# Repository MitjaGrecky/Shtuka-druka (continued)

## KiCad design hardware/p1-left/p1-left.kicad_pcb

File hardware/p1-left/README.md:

# P1 - Left deck (time column)

19 buttons with 2 RGB each (P101), an I2C multiplexer (P99), the deck bus to P2 (P100) and the module buses to M3 and W1.
Spec: `hardware/for-routing/SPEC_boards.md`, section P1. Status: rev 0.2 by the Rev 0.2 section below (R170, 16.11.2026; commit `decdae9`) - schematic and placed board, not routed (`UNROUTED`). Generator `REV` and the silk text still say 0.1 (not bumped in `decdae9`): the schematic owner should set `REV = "0.2"` and regenerate.
Package: `hardware/for-routing/P1/`. P99, P100, P101 are proposals: change them through the constants in `gen/design.py`.

| | |
|---|---|
| Board | 92 x 258 mm, 2 layers; panel x 10-102, y 4-262 |
| Top side | 19 x TS-1187A (C318884): Rec, Play, Stop, Restart, Metronome, Tap, Capture, Resample, Undo, Redo, Delete, Duplicate, Double, New, Quantize, Length, Automate, Repeat, Accent at their layout_v7 places; 38 x XL-1615RGBC-RF 6.5 mm left and right |
| Bottom side | 2 x LP5864 (U1 cell A 0x40: buttons 1-12, U2 cell B 0x41: 13-19) among their buttons; 3 x 74HC165 near their rows; TCA9546APWR (U6) near J1 |
| Buses | J1 2 x 8 to P2 at the right edge (P100: pins 1-14 as the module bus, 15 AUX unused, 16 GND); J2 2 x 7 to M3 and J3 2 x 7 to W1 at the rear edge |
| I2C | TCA9546A 0x70 (A2 A1 A0 via 0R to GND): ch 0 own LP5864s, ch 1 J2 (M3), ch 2 J3 (W1), ch 3 free; 4.7k pull-ups on ch 0-2, upstream pull-ups on P2 |
| Shift chain | P2 reads U3 (D7 Rec ... ), U4, U5 (bits 20-24 read 1), then M3 (J2), then W1 (J3), which continues to M5; W1's SR_IN pulled up here (R1); J1 pin 14 unused |
| ~INT | J2 and J3 ~INT go straight to J1 |
| Holes | 14 x M2: corners, short-side middles, long sides at rows without buttons (y 60, 97.5, 150, 197.5), at most 60 mm apart |

Checks (13.11.2026, PC): EasyEDA Pro import (project P1_v1): PCB 83/83 and schematic 83/83 nets, 110/110 parts, against a
reference netlist written from `design.py`. ERC, DRC, parity: CI (kicad-cli crashes this PC). No `schematic.pdf`/`outline.dxf` yet.
The TCA9546A symbol is converted from KiCad 10's library to the KiCad 7 format by `hardware/common/gen/sym7.py`.

Open: LCSC number of TCA9546APWR (to choose, P99); J2/J3 places at the rear edge follow M3's and W1's connectors (both near panel x 56) - set apart (x 40 and 72) so the two ribbons do not collide.

Generators: `gen/design.py`, `gen/make_sch.py`, `gen/check_netlist.py`, `gen/make_pcb.py` (shared blocks: `hardware/common/gen/kit.py` - `deck_inputs`, `i2c_mux`, `deck_bus`).

License: CERN-OHL-S-2.0 (hardware), AGPL-3.0-or-later (scripts).

Rev 0.2 (16.11.2026): R170 (16.11.2026): шинные разъёмы снизу лежачие (угловые): HX PZ1.27-2x7P WZ / 2x8P WZ (C22438113 / C22438114), J1 открыт к P2 (у P1 вправо, у P3 и P4 влево), J2–J4 к заднему краю; на P4 штекер колеса — JST S2B-PH-K-S (C173752, 179 611 шт.). Вертикальная вилка с IDC (≈ 7,5 мм) при 8 мм до дна не оставляла места на изгиб кабеля.

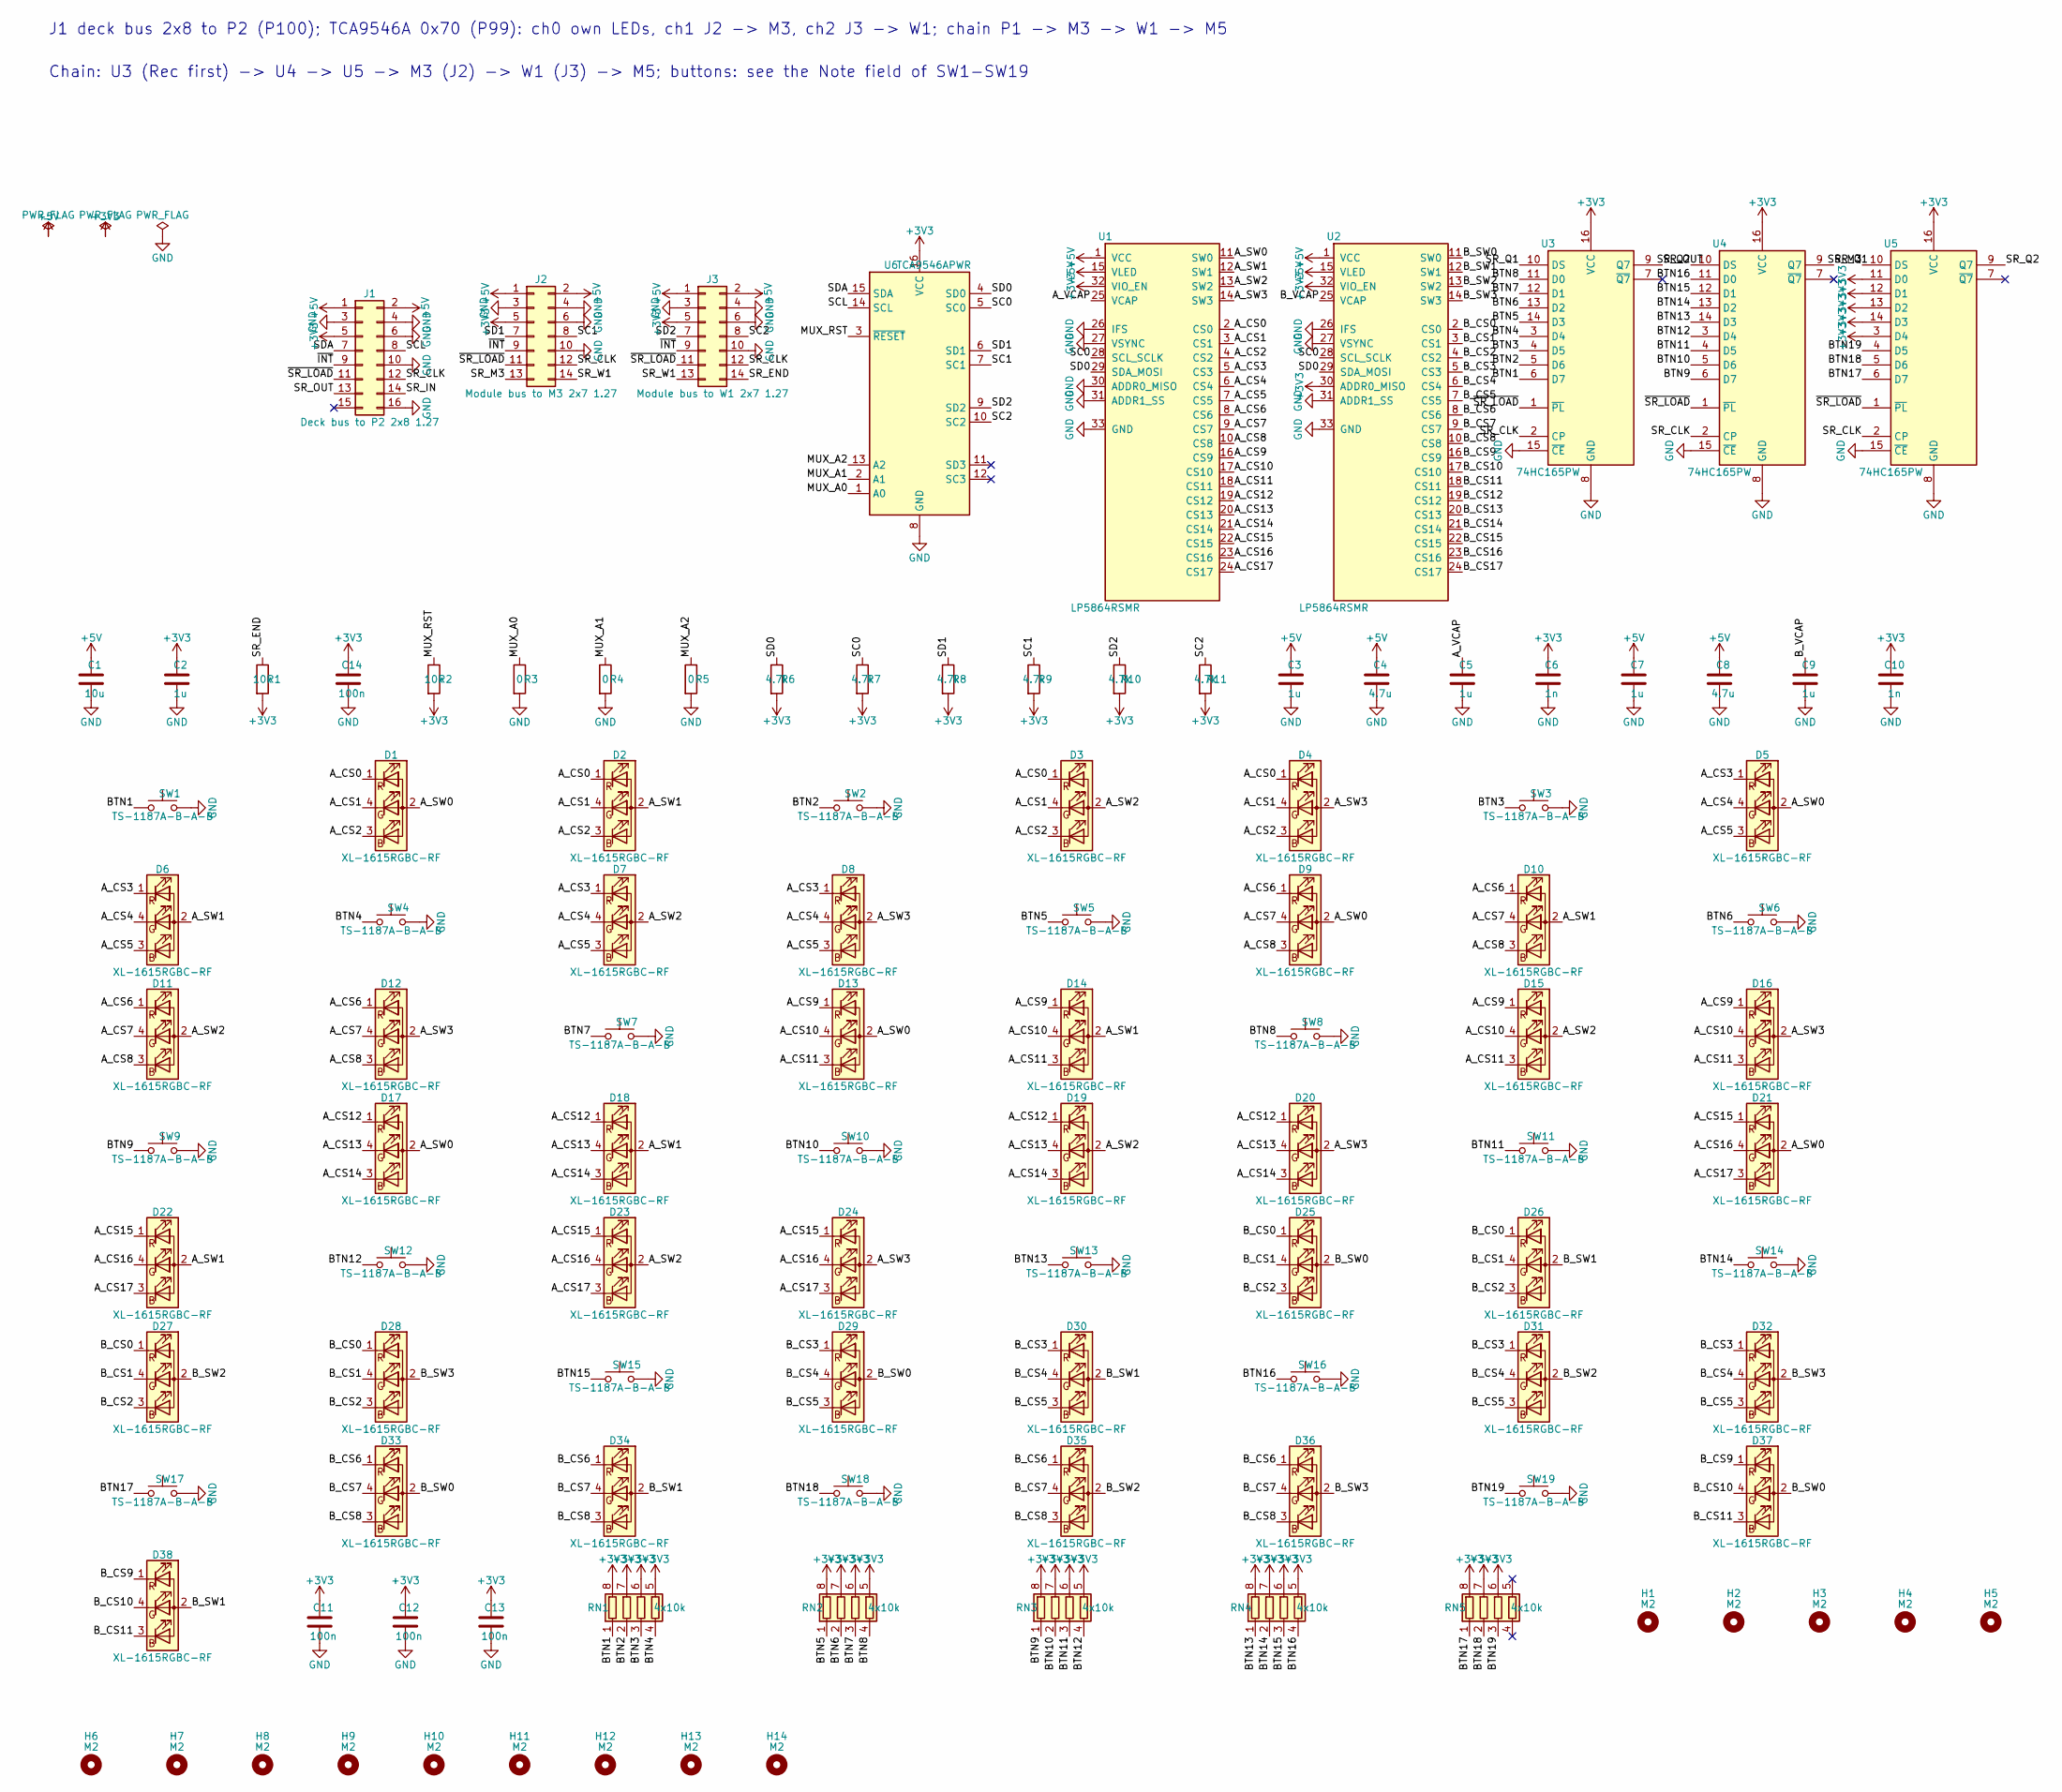
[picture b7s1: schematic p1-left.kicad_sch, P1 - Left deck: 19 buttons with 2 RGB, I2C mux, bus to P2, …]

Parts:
C1: 10u; C_0805_2012Metric; LCSC C15850
C2, C3, C5, C7, C9: 1u; C_0402_1005Metric; LCSC C52923
C4, C8: 4.7u; C_0805_2012Metric; LCSC C1779
C6, C10: 1n; C_0402_1005Metric; LCSC C1523
C11, C12, C13, C14: 100n; C_0402_1005Metric; LCSC C1525
D1, D2, D3, D4, D5, D6, D7, D8, D9, D10, D11, D12, D13, D14, D15, D16, D17, D18, D19, D20, D21, D22, D23, D24, D25, D26, D27, D28, D29, D30, D31, D32, D33, D34, D35, D36, D37, D38: XL-1615RGBC-RF; LED_RGB_XL-1615RGBC_1.6x1.5mm; LCSC C965840
H1, H2, H3, H4, H5, H6, H7, H8, H9, H10, H11, H12, H13, H14: M2; MountingHole_2.2mm_M2
J1: Deck bus to P2 2x8 1.27; PinHeader_2x08_P1.27mm_Horizontal; LCSC C22438114
J2: Module bus to M3 2x7 1.27; PinHeader_2x07_P1.27mm_Horizontal; LCSC C22438113
J3: Module bus to W1 2x7 1.27; PinHeader_2x07_P1.27mm_Horizontal; LCSC C22438113
R1, R2: 10k; R_0402_1005Metric; LCSC C25744
R3, R4, R5: 0; R_0402_1005Metric; LCSC C17168
R6, R7, R8, R9, R10, R11: 4.7k; R_0402_1005Metric; LCSC C25900
RN1, RN2, RN3, RN4, RN5: 4x10k; R_Array_Convex_4x0402; LCSC C25725
SW1, SW2, SW3, SW4, SW5, SW6, SW7, SW8, SW9, SW10, SW11, SW12, SW13, SW14, SW15, SW16, SW17, SW18, SW19: TS-1187A-B-A-B; SW_Push_1P1T_XKB_TS-1187A; LCSC C318884
U1, U2: LP5864RSMR; VQFN-32-1EP_4x4mm_P0.4mm_EP2.8x2.8mm; LCSC C5220564
U3, U4, U5: 74HC165PW; TSSOP-16_4.4x5mm_P0.65mm; LCSC C80696
U6: TCA9546APWR; TSSOP-16_4.4x5mm_P0.65mm; LCSC C201653

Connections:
+3V3: C2.1, C6.1, C10.1, C11.1, C12.1, C13.1, C14.1, J1.5, J2.5, J3.5, R1.2, R2.2, R6.2, R7.2, R8.2, R9.2, R10.2, R11.2, RN1.5 (R4.2), RN1.6 (R3.2), RN1.7 (R2.2), RN1.8 (R1.2), RN2.5 (R4.2), RN2.6 (R3.2), RN2.7 (R2.2), RN2.8 (R1.2), RN3.5 (R4.2), RN3.6 (R3.2), RN3.7 (R2.2), RN3.8 (R1.2), RN4.5 (R4.2), RN4.6 (R3.2), RN4.7 (R2.2), RN4.8 (R1.2), RN5.6 (R3.2), RN5.7 (R2.2), RN5.8 (R1.2), U1.32 (VIO_EN), U2.30 (ADDR0_MISO), U2.32 (VIO_EN), U3.16 (VCC), U4.16 (VCC), U5.3 (D4), U5.11 (D0), U5.12 (D1), U5.13 (D2), U5.14 (D3), U5.16 (VCC), U6.16 (VCC)
+5V: C1.1, C3.1, C4.1, C7.1, C8.1, J1.1, J1.2, J2.1, J2.2, J3.1, J3.2, U1.1 (VCC), U1.15 (VLED), U2.1 (VCC), U2.15 (VLED)
/A_CS0: D1.1 (RK), D2.1 (RK), D3.1 (RK), D4.1 (RK), U1.2 (CS0)
/A_CS1: D1.4 (GK), D2.4 (GK), D3.4 (GK), D4.4 (GK), U1.3 (CS1)
/A_CS2: D1.3 (BK), D2.3 (BK), D3.3 (BK), D4.3 (BK), U1.4 (CS2)
/A_CS3: D5.1 (RK), D6.1 (RK), D7.1 (RK), D8.1 (RK), U1.5 (CS3)
/A_CS4: D5.4 (GK), D6.4 (GK), D7.4 (GK), D8.4 (GK), U1.6 (CS4)
/A_CS5: D5.3 (BK), D6.3 (BK), D7.3 (BK), D8.3 (BK), U1.7 (CS5)
/A_CS6: D9.1 (RK), D10.1 (RK), D11.1 (RK), D12.1 (RK), U1.8 (CS6)
/A_CS7: D9.4 (GK), D10.4 (GK), D11.4 (GK), D12.4 (GK), U1.9 (CS7)
/A_CS8: D9.3 (BK), D10.3 (BK), D11.3 (BK), D12.3 (BK), U1.10 (CS8)
/A_CS9: D13.1 (RK), D14.1 (RK), D15.1 (RK), D16.1 (RK), U1.16 (CS9)
/A_CS10: D13.4 (GK), D14.4 (GK), D15.4 (GK), D16.4 (GK), U1.17 (CS10)
/A_CS11: D13.3 (BK), D14.3 (BK), D15.3 (BK), D16.3 (BK), U1.18 (CS11)
/A_CS12: D17.1 (RK), D18.1 (RK), D19.1 (RK), D20.1 (RK), U1.19 (CS12)
/A_CS13: D17.4 (GK), D18.4 (GK), D19.4 (GK), D20.4 (GK), U1.20 (CS13)
/A_CS14: D17.3 (BK), D18.3 (BK), D19.3 (BK), D20.3 (BK), U1.21 (CS14)
/A_CS15: D21.1 (RK), D22.1 (RK), D23.1 (RK), D24.1 (RK), U1.22 (CS15)
/A_CS16: D21.4 (GK), D22.4 (GK), D23.4 (GK), D24.4 (GK), U1.23 (CS16)
/A_CS17: D21.3 (BK), D22.3 (BK), D23.3 (BK), D24.3 (BK), U1.24 (CS17)
/A_SW0: D1.2 (A), D5.2 (A), D9.2 (A), D13.2 (A), D17.2 (A), D21.2 (A), U1.11 (SW0)
/A_SW1: D2.2 (A), D6.2 (A), D10.2 (A), D14.2 (A), D18.2 (A), D22.2 (A), U1.12 (SW1)
/A_SW2: D3.2 (A), D7.2 (A), D11.2 (A), D15.2 (A), D19.2 (A), D23.2 (A), U1.13 (SW2)
/A_SW3: D4.2 (A), D8.2 (A), D12.2 (A), D16.2 (A), D20.2 (A), D24.2 (A), U1.14 (SW3)
/A_VCAP: C5.1, U1.25 (VCAP)
/BTN1: RN1.1 (R1.1), SW1.1, U3.6 (D7)
/BTN2: RN1.2 (R2.1), SW2.1, U3.5 (D6)
/BTN3: RN1.3 (R3.1), SW3.1, U3.4 (D5)
/BTN4: RN1.4 (R4.1), SW4.1, U3.3 (D4)
/BTN5: RN2.1 (R1.1), SW5.1, U3.14 (D3)
/BTN6: RN2.2 (R2.1), SW6.1, U3.13 (D2)
/BTN7: RN2.3 (R3.1), SW7.1, U3.12 (D1)
/BTN8: RN2.4 (R4.1), SW8.1, U3.11 (D0)
/BTN9: RN3.1 (R1.1), SW9.1, U4.6 (D7)
/BTN10: RN3.2 (R2.1), SW10.1, U4.5 (D6)
/BTN11: RN3.3 (R3.1), SW11.1, U4.4 (D5)
/BTN12: RN3.4 (R4.1), SW12.1, U4.3 (D4)
/BTN13: RN4.1 (R1.1), SW13.1, U4.14 (D3)
/BTN14: RN4.2 (R2.1), SW14.1, U4.13 (D2)
/BTN15: RN4.3 (R3.1), SW15.1, U4.12 (D1)
/BTN16: RN4.4 (R4.1), SW16.1, U4.11 (D0)
/BTN17: RN5.1 (R1.1), SW17.1, U5.6 (D7)
/BTN18: RN5.2 (R2.1), SW18.1, U5.5 (D6)
/BTN19: RN5.3 (R3.1), SW19.1, U5.4 (D5)
/B_CS0: D25.1 (RK), D26.1 (RK), D27.1 (RK), D28.1 (RK), U2.2 (CS0)
/B_CS1: D25.4 (GK), D26.4 (GK), D27.4 (GK), D28.4 (GK), U2.3 (CS1)
/B_CS2: D25.3 (BK), D26.3 (BK), D27.3 (BK), D28.3 (BK), U2.4 (CS2)
/B_CS3: D29.1 (RK), D30.1 (RK), D31.1 (RK), D32.1 (RK), U2.5 (CS3)
/B_CS4: D29.4 (GK), D30.4 (GK), D31.4 (GK), D32.4 (GK), U2.6 (CS4)
/B_CS5: D29.3 (BK), D30.3 (BK), D31.3 (BK), D32.3 (BK), U2.7 (CS5)
/B_CS6: D33.1 (RK), D34.1 (RK), D35.1 (RK), D36.1 (RK), U2.8 (CS6)
/B_CS7: D33.4 (GK), D34.4 (GK), D35.4 (GK), D36.4 (GK), U2.9 (CS7)
/B_CS8: D33.3 (BK), D34.3 (BK), D35.3 (BK), D36.3 (BK), U2.10 (CS8)
/B_CS9: D37.1 (RK), D38.1 (RK), U2.16 (CS9)
/B_CS10: D37.4 (GK), D38.4 (GK), U2.17 (CS10)
/B_CS11: D37.3 (BK), D38.3 (BK), U2.18 (CS11)
/B_CS12: U2.19 (CS12)
/B_CS13: U2.20 (CS13)
/B_CS14: U2.21 (CS14)
/B_CS15: U2.22 (CS15)
/B_CS16: U2.23 (CS16)
/B_CS17: U2.24 (CS17)
/B_SW0: D25.2 (A), D29.2 (A), D33.2 (A), D37.2 (A), U2.11 (SW0)
/B_SW1: D26.2 (A), D30.2 (A), D34.2 (A), D38.2 (A), U2.12 (SW1)
/B_SW2: D27.2 (A), D31.2 (A), D35.2 (A), U2.13 (SW2)
/B_SW3: D28.2 (A), D32.2 (A), D36.2 (A), U2.14 (SW3)
/B_VCAP: C9.1, U2.25 (VCAP)
/MUX_A0: R3.1, U6.1 (A0)
/MUX_A1: R4.1, U6.2 (A1)
/MUX_A2: R5.1, U6.13 (A2)
/MUX_RST: R2.1, U6.3 (~RESET)
/SC0: R7.1, U1.28 (SCL_SCLK), U2.28 (SCL_SCLK), U6.5 (SC0)
/SC1: J2.8, R9.1, U6.7 (SC1)
/SC2: J3.8, R11.1, U6.10 (SC2)
/SCL: J1.8, U6.14 (SCL)
/SD0: R6.1, U1.29 (SDA_MOSI), U2.29 (SDA_MOSI), U6.4 (SD0)
/SD1: J2.7, R8.1, U6.6 (SD1)
/SD2: J3.7, R10.1, U6.9 (SD2)
/SDA: J1.7, U6.15 (SDA)
/SR_CLK: J1.12, J2.12, J3.12, U3.2 (CP), U4.2 (CP), U5.2 (CP)
/SR_END: J3.14, R1.1
/SR_IN: J1.14
/SR_M3: J2.13, U5.10 (DS)
/SR_OUT: J1.13, U3.9 (Q7)
/SR_Q1: U3.10 (DS), U4.9 (Q7)
/SR_Q2: U4.10 (DS), U5.9 (Q7)
/SR_W1: J2.14, J3.13
/~INT: J1.9, J2.9, J3.9
/~SR_LOAD: J1.11, J2.11, J3.11, U3.1 (~PL), U4.1 (~PL), U5.1 (~PL)
GND: C1.2, C2.2, C3.2, C4.2, C5.2, C6.2, C7.2, C8.2, C9.2, C10.2, C11.2, C12.2, C13.2, C14.2, J1.3, J1.4, J1.6, J1.10, J1.16, J2.3, J2.4, J2.6, J2.10, J3.3, J3.4, J3.6, J3.10, R3.2, R4.2, R5.2, SW1.2, SW2.2, SW3.2, SW4.2, SW5.2, SW6.2, SW7.2, SW8.2, SW9.2, SW10.2, SW11.2, SW12.2, SW13.2, SW14.2, SW15.2, SW16.2, SW17.2, SW18.2, SW19.2, U1.26 (IFS), U1.27 (VSYNC), U1.30 (ADDR0_MISO), U1.31 (ADDR1_SS), U1.33 (GND), U2.26 (IFS), U2.27 (VSYNC), U2.31 (ADDR1_SS), U2.33 (GND), U3.8 (GND), U3.15 (~CE), U4.8 (GND), U4.15 (~CE), U5.8 (GND), U5.15 (~CE), U6.8 (GND)

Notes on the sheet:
J1 deck bus 2x8 to P2 (P100); TCA9546A 0x70 (P99): ch0 own LEDs, ch1 J2 -> M3, ch2 J3 -> W1; chain P1 -> M3 -> W1 -> M5
Chain: U3 (Rec first) -> U4 -> U5 -> M3 (J2) -> W1 (J3) -> M5; buttons: see the Note field of SW1-SW19

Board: 2 copper layers, 110 parts (39 on the bottom side), 83 nets, no tracks yet.

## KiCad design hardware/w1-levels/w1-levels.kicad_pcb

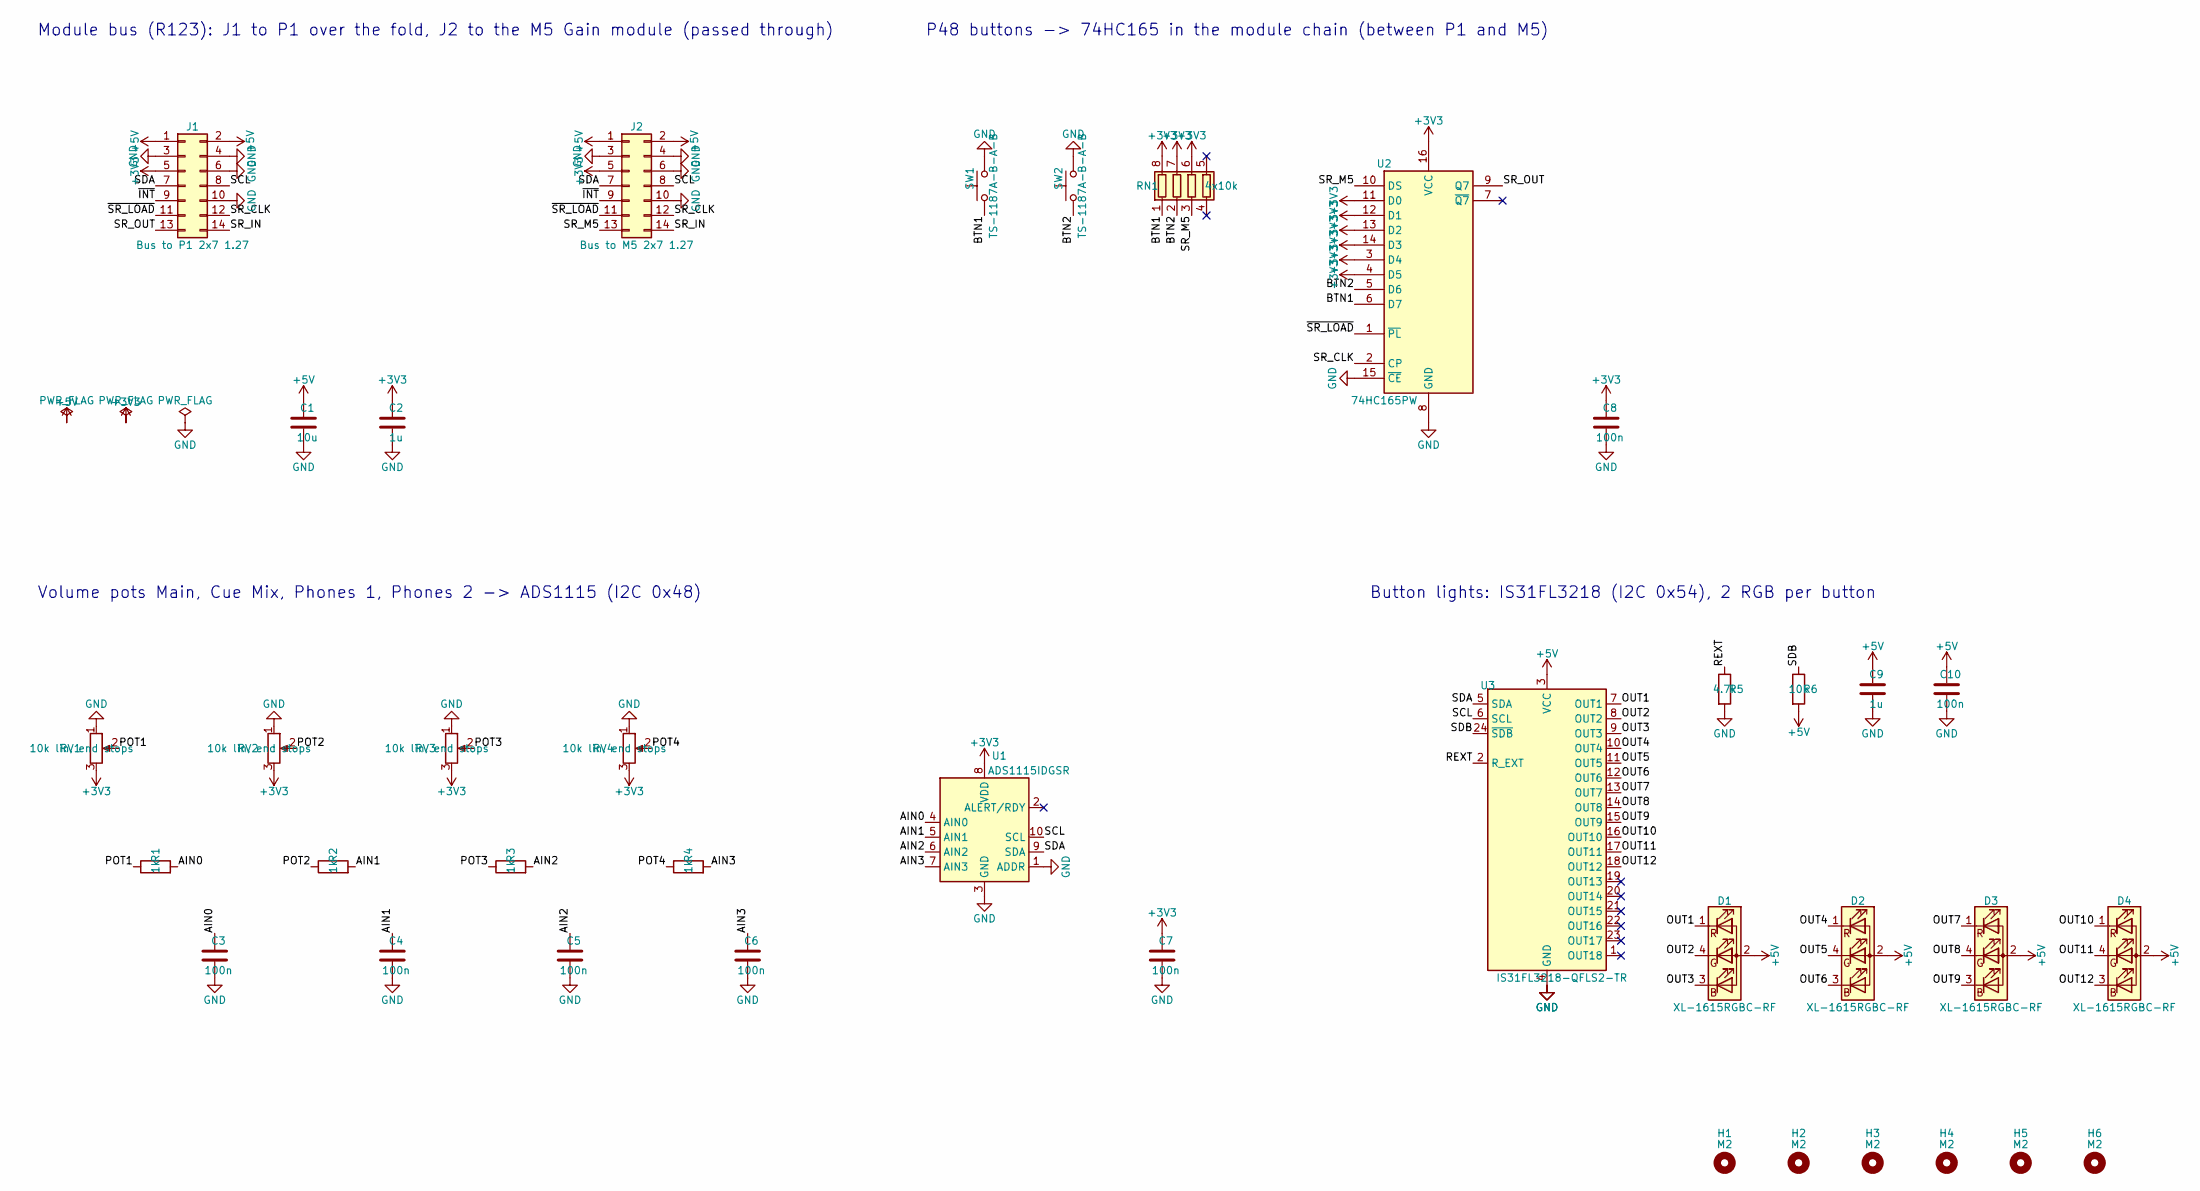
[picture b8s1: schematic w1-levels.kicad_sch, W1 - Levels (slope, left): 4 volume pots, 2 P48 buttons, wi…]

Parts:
C1: 10u; C_0805_2012Metric; LCSC C15850
C2, C9: 1u; C_0402_1005Metric; LCSC C52923
C3, C4, C5, C6, C7, C8, C10: 100n; C_0402_1005Metric; LCSC C1525
D1, D2, D3, D4: XL-1615RGBC-RF; LED_RGB_XL-1615RGBC_1.6x1.5mm; LCSC C965840
H1, H2, H3, H4, H5, H6: M2; MountingHole_2.2mm_M2
J1: Bus to P1 2x7 1.27; PinHeader_2x07_P1.27mm_Vertical; LCSC C5372811
J2: Bus to M5 2x7 1.27; PinHeader_2x07_P1.27mm_Vertical; LCSC C5372811
R1, R2, R3, R4: 1k; R_0402_1005Metric; LCSC C11702
R5: 4.7k; R_0402_1005Metric; LCSC C25900
R6: 10k; R_0402_1005Metric; LCSC C25744
RN1: 4x10k; R_Array_Convex_4x0402; LCSC C25725
RV1, RV2, RV3, RV4: 10k lin, end stops; Potentiometer_Alps_RK09K_Single_Vertical; Part Alps RK09K1130A5R (shaft; was A6S, rev 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; LCSC C209779
SW1, SW2: TS-1187A-B-A-B; SW_Push_1P1T_XKB_TS-1187A; LCSC C318884
U1: ADS1115IDGSR; TSSOP-10_3x3mm_P0.5mm; LCSC C37593
U2: 74HC165PW; TSSOP-16_4.4x5mm_P0.65mm; LCSC C80696
U3: IS31FL3218-QFLS2-TR; QFN-24-1EP_4x4mm_P0.5mm_EP2.7x2.7mm; LCSC C2940546

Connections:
+3V3: C2.1, C7.1, C8.1, J1.5, J2.5, RN1.6 (R3.2), RN1.7 (R2.2), RN1.8 (R1.2), RV1.3, RV2.3, RV3.3, RV4.3, U1.8 (VDD), U2.3 (D4), U2.4 (D5), U2.11 (D0), U2.12 (D1), U2.13 (D2), U2.14 (D3), U2.16 (VCC)
+5V: C1.1, C9.1, C10.1, D1.2 (A), D2.2 (A), D3.2 (A), D4.2 (A), J1.1, J1.2, J2.1, J2.2, R6.2, U3.3 (VCC)
/AIN0: C3.1, R1.2, U1.4 (AIN0)
/AIN1: C4.1, R2.2, U1.5 (AIN1)
/AIN2: C5.1, R3.2, U1.6 (AIN2)
/AIN3: C6.1, R4.2, U1.7 (AIN3)
/BTN1: RN1.1 (R1.1), SW1.1, U2.6 (D7)
/BTN2: RN1.2 (R2.1), SW2.1, U2.5 (D6)
/OUT1: D1.1 (RK), U3.7 (OUT1)
/OUT2: D1.4 (GK), U3.8 (OUT2)
/OUT3: D1.3 (BK), U3.9 (OUT3)
/OUT4: D2.1 (RK), U3.10 (OUT4)
/OUT5: D2.4 (GK), U3.11 (OUT5)
/OUT6: D2.3 (BK), U3.12 (OUT6)
/OUT7: D3.1 (RK), U3.13 (OUT7)
/OUT8: D3.4 (GK), U3.14 (OUT8)
/OUT9: D3.3 (BK), U3.15 (OUT9)
/OUT10: D4.1 (RK), U3.16 (OUT10)
/OUT11: D4.4 (GK), U3.17 (OUT11)
/OUT12: D4.3 (BK), U3.18 (OUT12)
/POT1: R1.1, RV1.2
/POT2: R2.1, RV2.2
/POT3: R3.1, RV3.2
/POT4: R4.1, RV4.2
/REXT: R5.1, U3.2 (R_EXT)
/SCL: J1.8, J2.8, U1.10 (SCL), U3.6 (SCL)
/SDA: J1.7, J2.7, U1.9 (SDA), U3.5 (SDA)
/SDB: R6.1, U3.24 (~SDB)
/SR_CLK: J1.12, J2.12, U2.2 (CP)
/SR_IN: J1.14, J2.14
/SR_M5: J2.13, RN1.3 (R3.1), U2.10 (DS)
/SR_OUT: J1.13, U2.9 (Q7)
/~INT: J1.9, J2.9
/~SR_LOAD: J1.11, J2.11, U2.1 (~PL)
GND: C1.2, C2.2, C3.2, C4.2, C5.2, C6.2, C7.2, C8.2, C9.2, C10.2, J1.3, J1.4, J1.6, J1.10, J2.3, J2.4, J2.6, J2.10, R5.2, RV1.1, RV2.1, RV3.1, RV4.1, SW1.2, SW2.2, U1.1 (ADDR), U1.3 (GND), U2.8 (GND), U2.15 (~CE), U3.4 (GND), U3.25 (GND)

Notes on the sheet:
Module bus (R123): J1 to P1 over the fold, J2 to the M5 Gain module (passed through)
Volume pots Main, Cue Mix, Phones 1, Phones 2 -> ADS1115 (I2C 0x48)
P48 buttons -> 74HC165 in the module chain (between P1 and M5)
Button lights: IS31FL3218 (I2C 0x54), 2 RGB per button

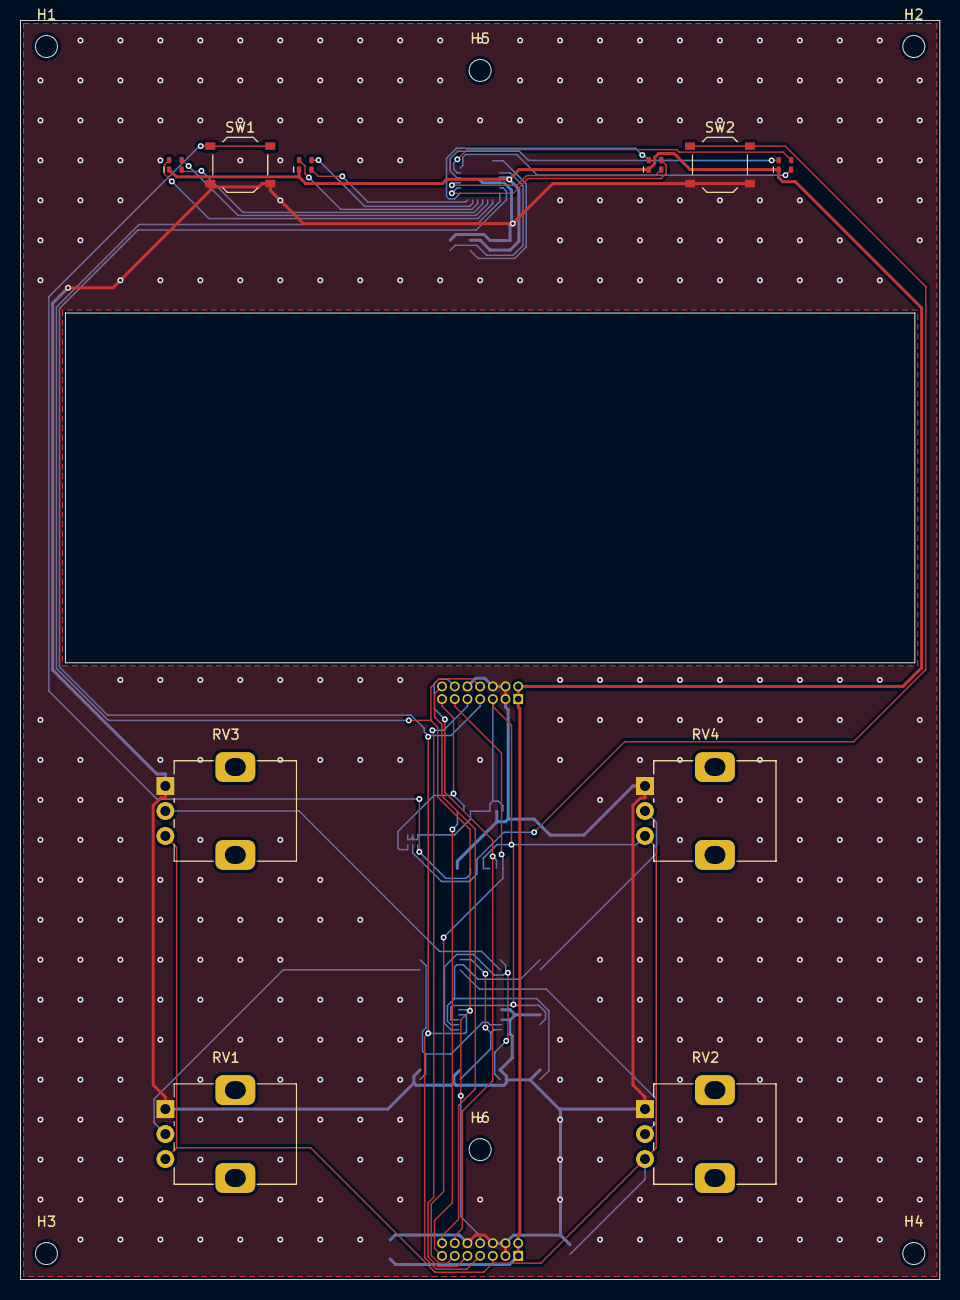
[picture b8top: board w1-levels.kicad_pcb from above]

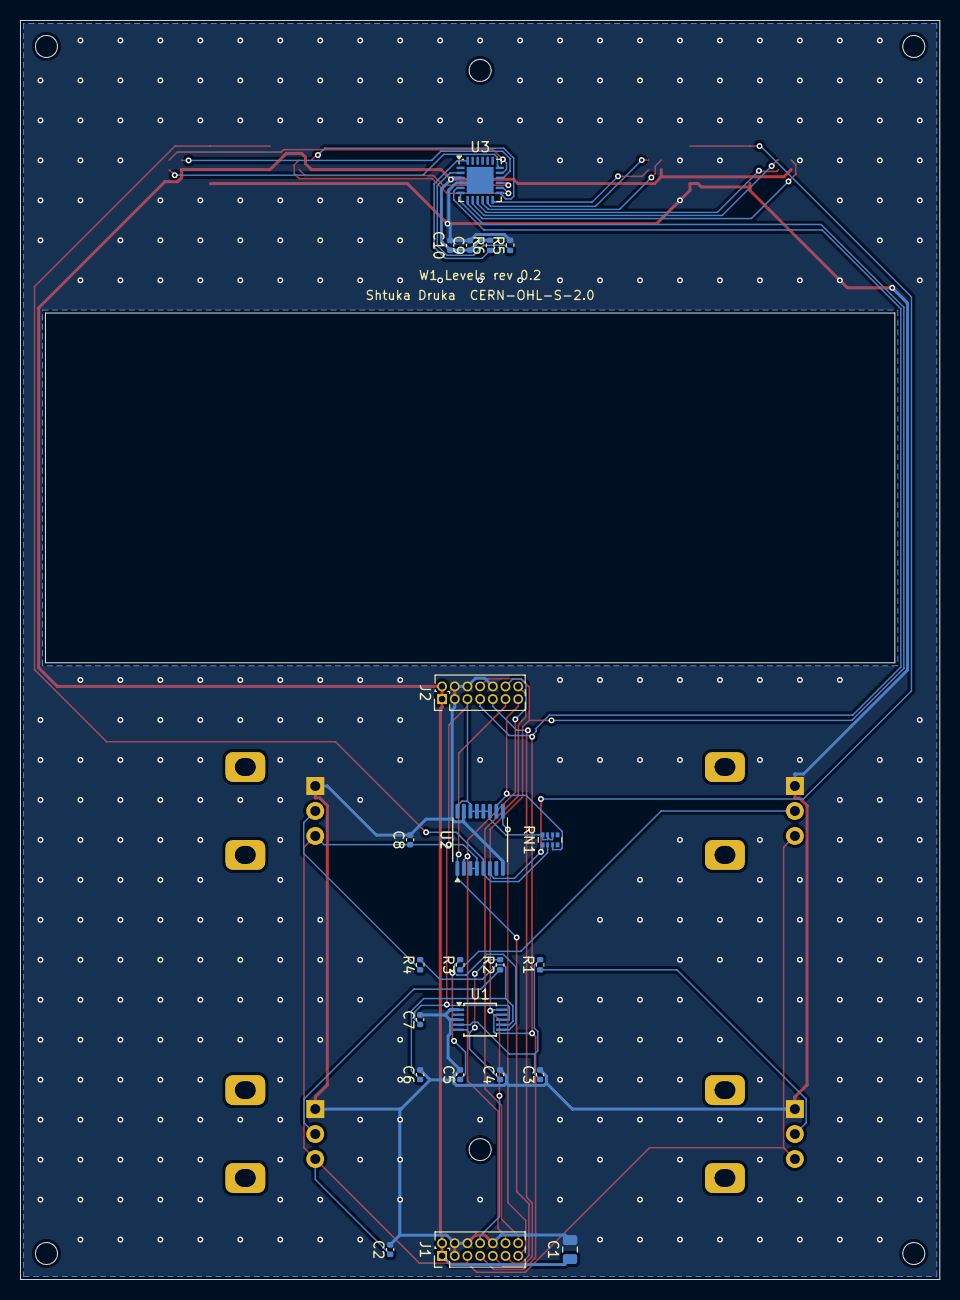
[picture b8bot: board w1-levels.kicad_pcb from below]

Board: 2 copper layers, 92.0 x 126.0 mm, 38 parts (22 on the bottom side), 35 nets.
